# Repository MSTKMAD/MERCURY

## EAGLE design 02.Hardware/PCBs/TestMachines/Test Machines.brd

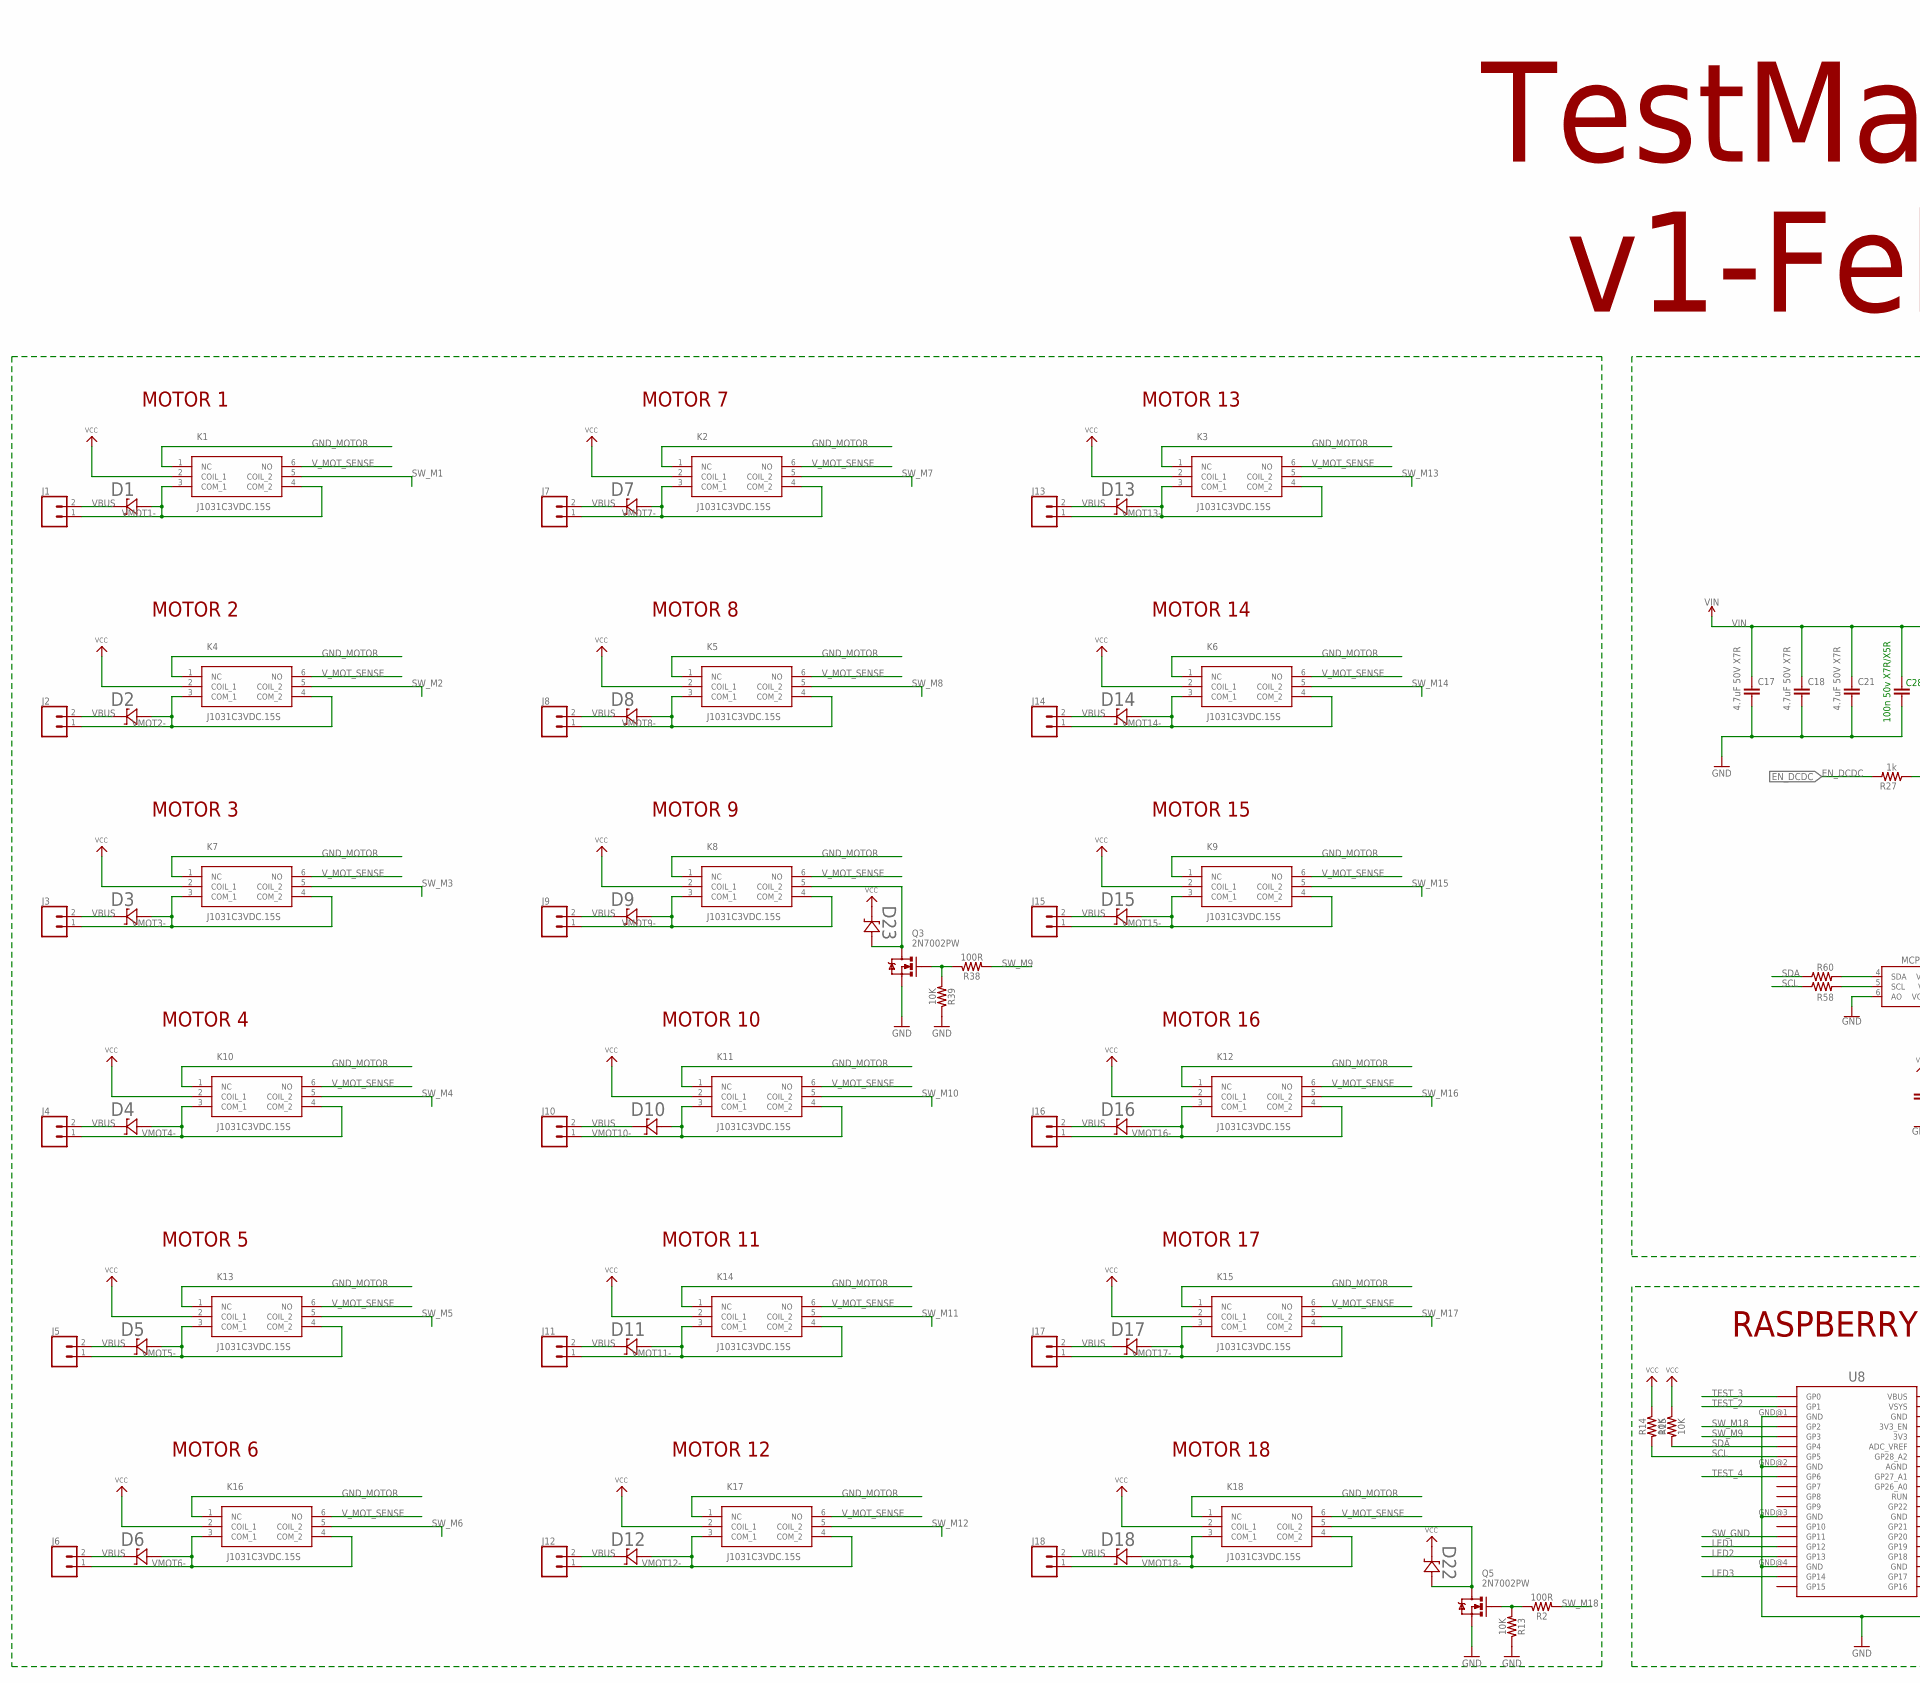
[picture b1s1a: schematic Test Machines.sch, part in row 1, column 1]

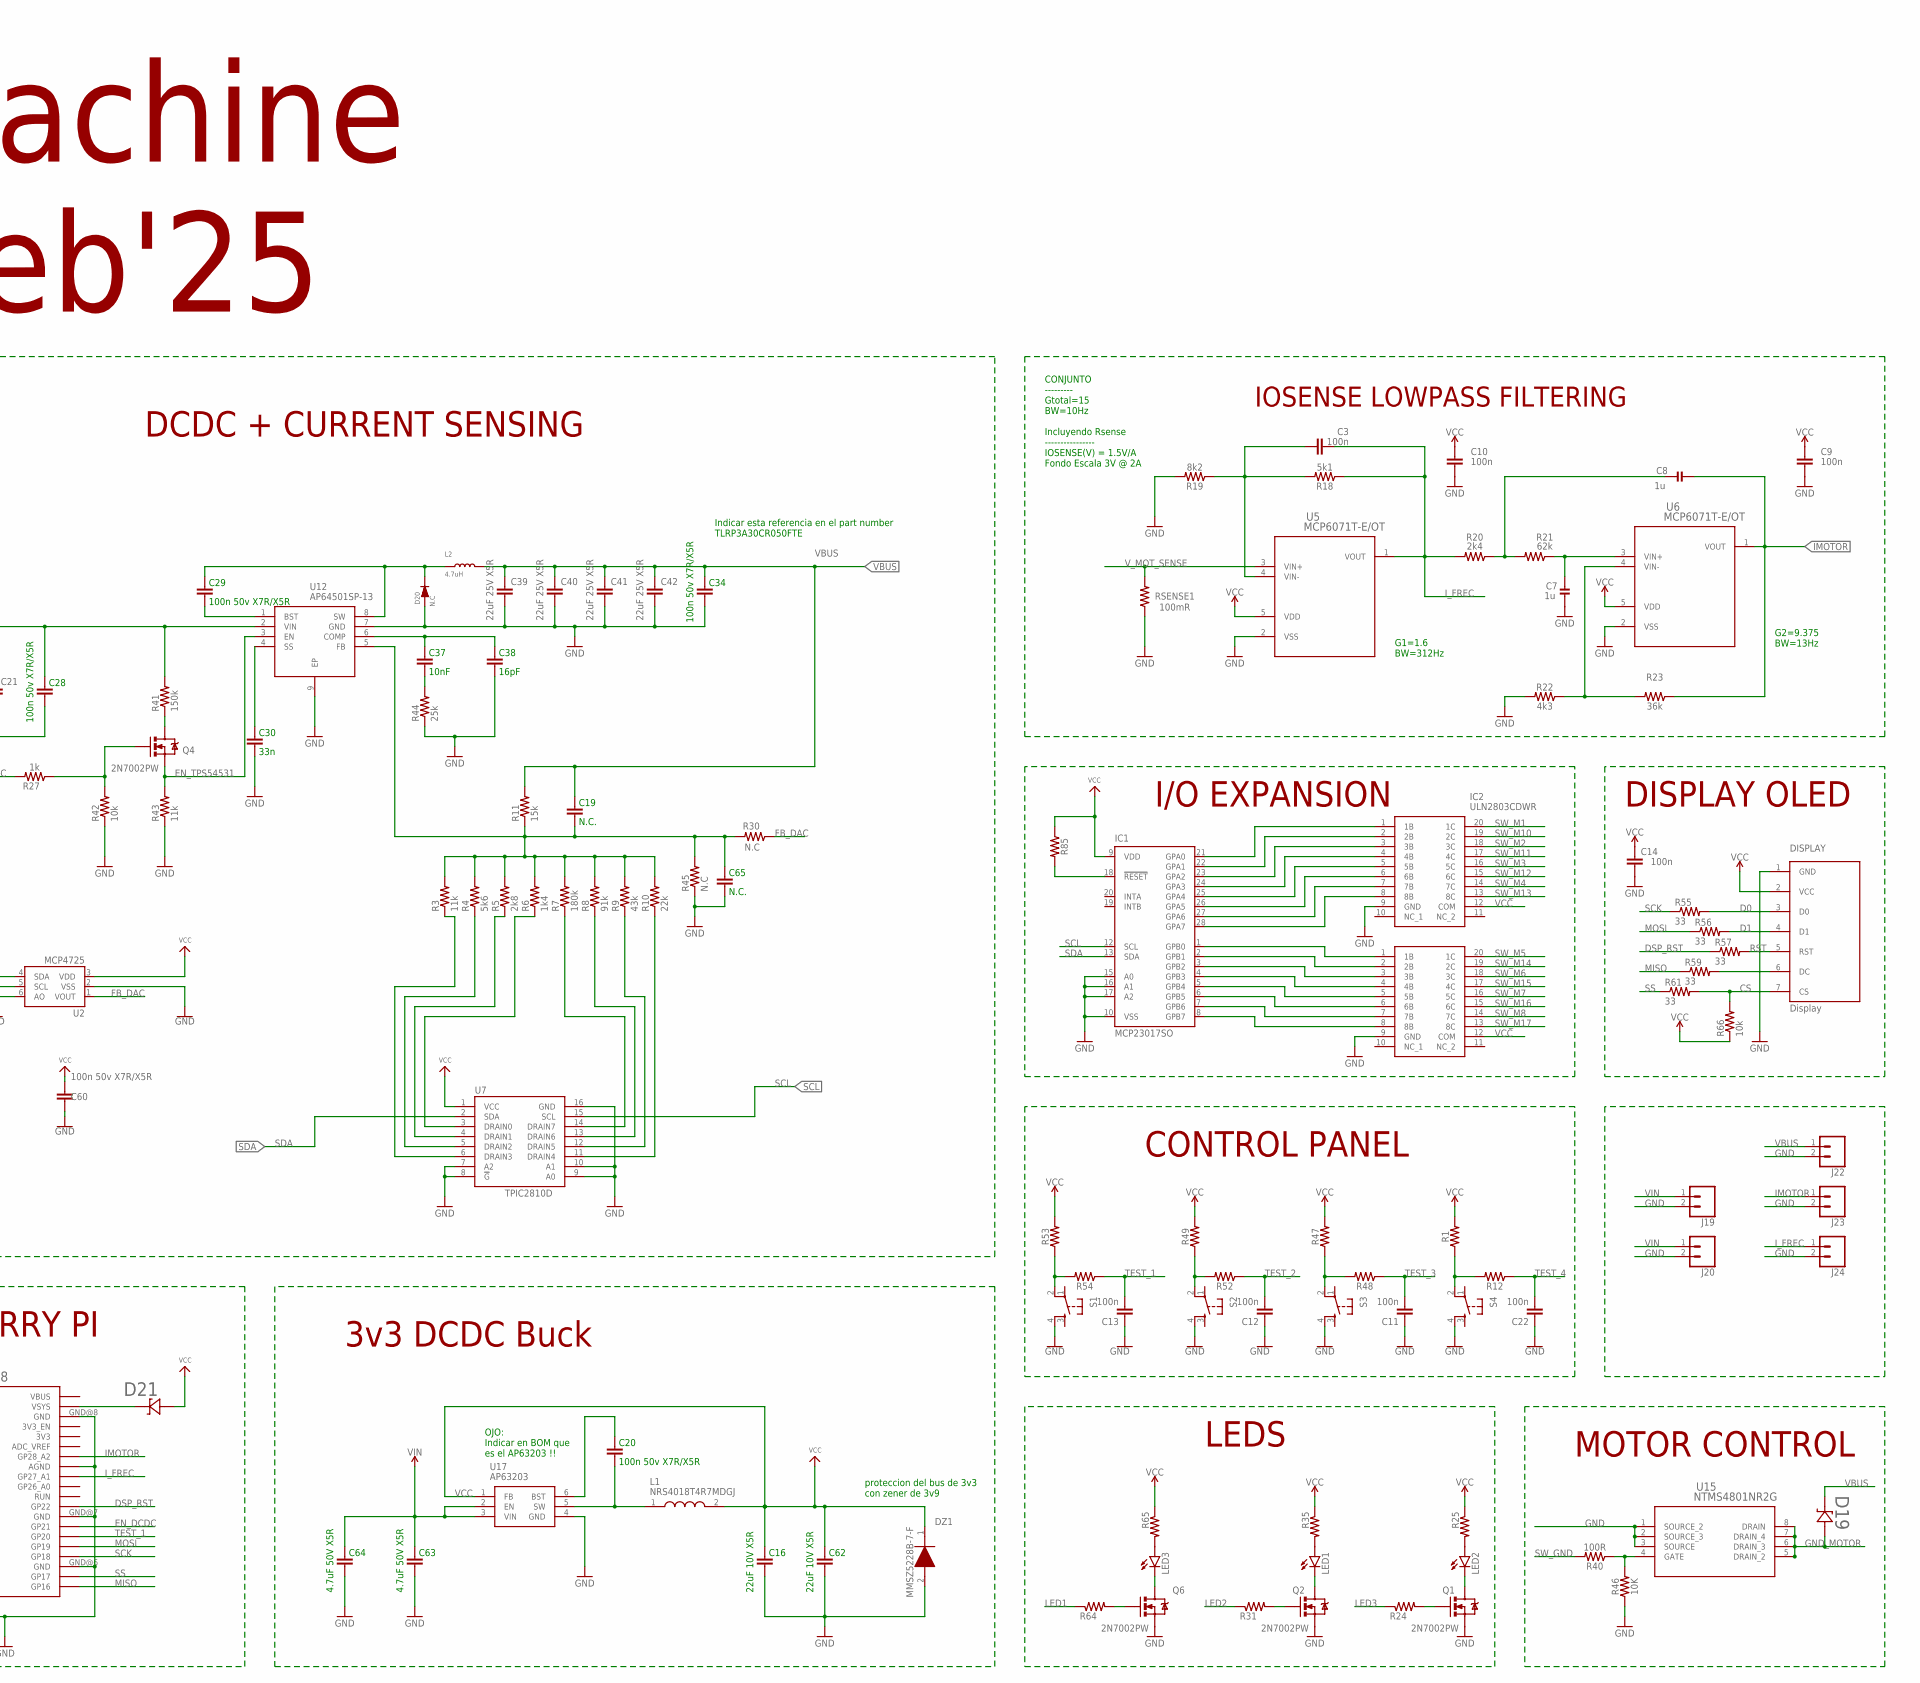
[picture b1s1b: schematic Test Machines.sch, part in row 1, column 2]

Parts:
C3, C9, C10: 100n; 0603
C7, C8: 1u; 0603-NO
C11, C12, C13, C14, C22: 100n; 0805
C16, C62: 22uF 10V X5R; 0805
C17, C18, C21: 4.7uF 50V X7R; 1210
C19, C65: N.C.; 0805
C20, C28, C29, C34, C60: 100n 50v X7R/X5R; 0805
C30: 33n; 0805
C37: 10nF; 0805
C38: 16pF; 0805
C39, C40, C41, C42: 22uF 25V X5R; 1210
C63, C64: 4.7uF 50V X5R; 0805
D1, D2, D3, D4, D5, D6, D7, D8, D9, D10, D11, D12, D13, D14, D15, D16, D17, D18, D19, D21, D22, D23: STPS1L40U; SMB_STM
D20: N.C; DO-214AB
DISPLAY: Display; OLED_LCD
DZ1: MMSZ5228B-7-F; SODFL3518X115N
IC1: MCP23017SO; SO28W
IC2, IC3: ULN2803CDWR; SOIC127P1030X265-20N
J1, J2, J3, J4, J5, J6, J7, J8, J9, J10, J11, J12, J13, J14, J15, J16, J17, J18, J19, J20, J22, J23, J24: CONN_02; 1X02
K1, K2, K3, K4, K5, K6, K7, K8, K9, K10, K11, K12, K13, K14, K15, K16, K17, K18: J1031C3VDC.15S; J1031C3VDC15S
L1: NRS4018T4R7MDGJ; NRS4018T100MDGJ
L2: 4.7uH; WE-LHMI
LED1, LED2, LED3: LED3MM
Q1, Q2, Q3, Q4, Q5, Q6: 2N7002PW; SOT323
R1, R12, R24, R25, R31, R35, R47, R48, R49, R52, R53, R54, R58, R60, R64, R65, R85: 0805
R2, R38, R40: 100R; 0805
R3, R43: 11k; 0805
R4: 5k6; 0805
R5: 2k8; 0805
R6: 1k4; 0805
R7: 180k; 0805
R8: 91k; 0805
R9: 43k; 0805
R10: 22k; 0805
R11: 15k; 0805
R13, R14, R15, R39, R46: 10K; 0805
R18: 5k1; 0805
R19: 8k2; 0805
R20: 2k4; 0805
R21: 62k; 0805
R22: 4k3; 0805
R23: 36k; 0805
R27: 1k; 0805
R30, R45: N.C; 0805
R41: 150k; 0805
R42, R66: 10k; 0805
R44: 25k; 0805
R55, R56, R57, R59, R61: 33; 0805
RSENSE1: 100mR; 1206
S1, S2, S3, S4: TAC_SWITCH_KSC931G-SMD; TAC_SW_SMD_KSC931G
U2: MCP4725; SOT23-6
U5, U6: MCP6071T-E/OT; SOT-23-5_MC_MCH
U7: TPIC2810D; SO16
U8: RPI_PICO_IG-TH; RPI_PICO_TH
U12: AP64501SP-13; SOIC127P600X163-9N
U15: NTMS4801NR2G; SOIC8_4X5_ONS
U17: AP63203; SOT95P280X100-6N

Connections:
CS: DISPLAY.7 (CS), R61.2, R66.2
D0: DISPLAY.3 (D0), R55.2
D1: DISPLAY.4 (D1), R56.2
DSP_RST: R57.1, U8.GP22
EN_DCDC: R27.2, U8.GP21
EN_TPS54531: Q4.2 (S), R43.2, U12.3 (EN)
FB_DAC: R30.1, U2.1 (VOUT)
GND: C7.2, C9.2, C10.2, C11.1, C12.1, C13.1, C14.2, C16.1, C17.2, C18.2, C21.2, C22.1, C28.1, C30.1, C34.1, C38.1, C39.2, C40.2, C41.2, C42.2, C60.1, C62.1, C63.1, C64.1, C65.1, D20.1 (A), DISPLAY.1 (GND), DZ1.2 (A), IC1.10 (VSS), IC1.15 (A0), IC1.16 (A1), IC1.17 (A2), IC2.9 (GND), IC3.9 (GND), J19.2, J20.2, J22.2, J23.2, J24.2, Q1.2 (S), Q2.2 (S), Q3.2 (S), Q5.2 (S), Q6.2 (S), R13.1, R19.2, R22.2, R39.1, R42.1, R43.1, R44.1, R45.1, R46.1, RSENSE1.1, S1.4, S2.4, S3.4, S4.4, U2.2 (VSS), U2.6 (AO), U5.2 (VSS), U6.2 (VSS), U7.7 (A2), U7.8 (!G), U7.9 (A0), U7.10 (A1), U7.16 (GND), U8.AGND, U8.GND@1 (GND), U8.GND@2 (GND), U8.GND@3 (GND), U8.GND@4 (GND), U8.GND@6 (GND), U8.GND@7 (GND), U8.GND@8 (GND), U12.7 (GND), U12.9 (EP), U15.1 (SOURCE_2), U15.2 (SOURCE_3), U15.3 (SOURCE), U17.4 (GND)
GND_MOTOR: D19.1, K1.1 (NC), K2.1 (NC), K3.1 (NC), K4.1 (NC), K5.1 (NC), K6.1 (NC), K7.1 (NC), K8.1 (NC), K9.1 (NC), K10.1 (NC), K11.1 (NC), K12.1 (NC), K13.1 (NC), K14.1 (NC), K15.1 (NC), K16.1 (NC), K17.1 (NC), K18.1 (NC), U15.5 (DRAIN_2), U15.6 (DRAIN_3), U15.7 (DRAIN_4), U15.8 (DRAIN)
IMOTOR: C8.2, J23.1, R23.1, U6.1 (VOUT), U8.GP28_A2
I_FREC: C3.1, J24.1, R18.1, R20.2, U5.1 (VOUT), U8.GP27_A1
LED1: R64.1, U8.GP12
LED2: R31.1, U8.GP13
LED3: R24.1, U8.GP14
MISO: R59.1, U8.GP16
MOSI: R56.1, U8.GP19
unnamed: R3.1, U7.6 (DRAIN3)
unnamed: R4.1, U7.5 (DRAIN2)
unnamed: R5.1, U7.4 (DRAIN1)
unnamed: R6.1, U7.3 (DRAIN0)
unnamed: R7.1, U7.14 (DRAIN7)
unnamed: R8.1, U7.13 (DRAIN6)
unnamed: R9.1, U7.12 (DRAIN5)
unnamed: R10.1, U7.11 (DRAIN4)
unnamed: R1.1, R12.2, S4.2
unnamed: LED1.A, R35.2
unnamed: LED1.K (C), Q2.3 (D)
unnamed: Q5.1 (G), R2.1, R13.2
unnamed: D22.1, K18.5 (COIL_2), Q5.3 (D)
unnamed: D23.1, K8.5 (COIL_2), Q3.3 (D)
unnamed: C3.2, R18.2, R19.1, U5.4 (VIN-)
unnamed: R22.1, R23.2, U6.4 (VIN-)
unnamed: C19.1, C65.2, R3.2, R4.2, R5.2, R6.2, R7.2, R8.2, R9.2, R10.2, R11.1, R30.2, R45.2, U12.5 (FB)
unnamed: C8.1, R20.1, R21.2
unnamed: Q2.1 (G), R31.2
unnamed: C7.1, R21.1, U6.3 (VIN+)
unnamed: Q1.1 (G), R24.2
unnamed: LED2.A, R25.2
unnamed: LED2.K (C), Q1.3 (D)
unnamed: Q3.1 (G), R38.1, R39.2
unnamed: R40.1, R46.2, U15.4 (GATE)
unnamed: Q4.3 (D), R41.1
unnamed: R47.1, R48.2, S3.2
unnamed: R49.1, R52.2, S2.2
unnamed: R53.1, R54.2, S1.2
unnamed: DISPLAY.6 (DC), R59.2
unnamed: C30.2, U12.4 (SS)
unnamed: R58.2, U2.5 (SCL)
unnamed: C29.1, U12.1 (BST)
unnamed: R60.2, U2.4 (SDA)
unnamed: C29.2, D20.2 (K), L2.1, U12.8 (SW)
unnamed: C37.2, C38.2, U12.6 (COMP)
unnamed: C37.1, R44.2
unnamed: Q6.1 (G), R64.2
unnamed: LED3.A, R65.2
unnamed: LED3.K (C), Q6.3 (D)
unnamed: C20.2, U17.6 (BST)
unnamed: C20.1, L1.1, U17.5 (SW)
unnamed: D21.2, U8.VSYS
unnamed: IC1.18 (!RESET), R85.2
unnamed: IC1.21 (GPA0), IC2.1 (1B)
unnamed: IC1.22 (GPA1), IC2.2 (2B)
unnamed: IC1.23 (GPA2), IC2.3 (3B)
unnamed: IC1.24 (GPA3), IC2.4 (4B)
unnamed: IC1.25 (GPA4), IC2.5 (5B)
unnamed: IC1.26 (GPA5), IC2.6 (6B)
unnamed: IC1.27 (GPA6), IC2.7 (7B)
unnamed: IC1.28 (GPA7), IC2.8 (8B)
unnamed: IC1.1 (GPB0), IC3.1 (1B)
unnamed: IC1.2 (GPB1), IC3.2 (2B)
unnamed: IC1.3 (GPB2), IC3.3 (3B)
unnamed: IC1.4 (GPB3), IC3.4 (4B)
unnamed: IC1.5 (GPB4), IC3.5 (5B)
unnamed: IC1.6 (GPB5), IC3.6 (6B)
unnamed: IC1.7 (GPB6), IC3.7 (7B)
unnamed: IC1.8 (GPB7), IC3.8 (8B)
RST: DISPLAY.5 (RST), R57.2
SAFETY_EN_DCDC: Q4.1 (G), R27.1, R42.2
SCK: R55.1, U8.GP18
SCL: IC1.12 (SCL), R14.2, R58.1, U7.15 (SCL), U8.GP5
SDA: IC1.13 (SDA), R15.2, R60.1, U7.2 (SDA), U8.GP4
SS: R61.1, U8.GP17
SW_GND: R40.2, U8.GP11
SW_M1: IC2.20 (1C), K1.5 (COIL_2)
SW_M2: IC2.18 (3C), K4.5 (COIL_2)
SW_M3: IC2.16 (5C), K7.5 (COIL_2)
SW_M4: IC2.14 (7C), K10.5 (COIL_2)
SW_M5: IC3.20 (1C), K13.5 (COIL_2)
SW_M6: IC3.18 (3C), K16.5 (COIL_2)
SW_M7: IC3.16 (5C), K2.5 (COIL_2)
SW_M8: IC3.14 (7C), K5.5 (COIL_2)
SW_M9: R38.2, U8.GP3
SW_M10: IC2.19 (2C), K11.5 (COIL_2)
SW_M11: IC2.17 (4C), K14.5 (COIL_2)
SW_M12: IC2.15 (6C), K17.5 (COIL_2)
SW_M13: IC2.13 (8C), K3.5 (COIL_2)
SW_M14: IC3.19 (2C), K6.5 (COIL_2)
SW_M15: IC3.17 (4C), K9.5 (COIL_2)
SW_M16: IC3.15 (6C), K12.5 (COIL_2)
SW_M17: IC3.13 (8C), K15.5 (COIL_2)
SW_M18: R2.2, U8.GP2
TEST_1: C13.2, R54.1, U8.GP20
TEST_2: C12.2, R52.1, U8.GP1
TEST_3: C11.2, R48.1, U8.GP0
TEST_4: C22.2, R12.1, U8.GP6
VBUS: C19.2, C34.2, C39.1, C40.1, C41.1, C42.1, D1.2, D2.2, D3.2, D4.2, D5.2, D6.2, D7.2, D8.2, D9.2, D10.2, D11.2, D12.2, D13.2, D14.2, D15.2, D16.2, D17.2, D18.2, D19.2, J1.2, J2.2, J3.2, J4.2, J5.2, J6.2, J7.2, J8.2, J9.2, J10.2, J11.2, J12.2, J13.2, J14.2, J15.2, J16.2, J17.2, J18.2, J22.1, L2.2, R11.2
VCC: C9.1, C10.1, C14.1, C16.2, C60.2, C62.2, D21.1, D22.2, D23.2, DISPLAY.2 (VCC), DZ1.1 (K), IC1.9 (VDD), IC2.12 (COM), IC3.12 (COM), K1.2 (COIL_1), K2.2 (COIL_1), K3.2 (COIL_1), K4.2 (COIL_1), K5.2 (COIL_1), K6.2 (COIL_1), K7.2 (COIL_1), K8.2 (COIL_1), K9.2 (COIL_1), K10.2 (COIL_1), K11.2 (COIL_1), K12.2 (COIL_1), K13.2 (COIL_1), K14.2 (COIL_1), K15.2 (COIL_1), K16.2 (COIL_1), K17.2 (COIL_1), K18.2 (COIL_1), L1.2, R1.2, R14.1, R15.1, R25.1, R35.1, R47.2, R49.2, R53.2, R65.1, R66.1, R85.1, U2.3 (VDD), U5.5 (VDD), U6.5 (VDD), U7.1 (VCC), U17.1 (FB)
VIN: C17.1, C18.1, C21.1, C28.2, C63.2, C64.2, J19.1, J20.1, R41.2, U12.2 (VIN), U17.2 (EN), U17.3 (VIN)
VMOT1-: D1.1, J1.1, K1.3 (COM_1), K1.4 (COM_2)
VMOT2-: D2.1, J2.1, K4.3 (COM_1), K4.4 (COM_2)
VMOT3-: D3.1, J3.1, K7.3 (COM_1), K7.4 (COM_2)
VMOT4-: D4.1, J4.1, K10.3 (COM_1), K10.4 (COM_2)
VMOT5-: D5.1, J5.1, K13.3 (COM_1), K13.4 (COM_2)
VMOT6-: D6.1, J6.1, K16.3 (COM_1), K16.4 (COM_2)
VMOT7-: D7.1, J7.1, K2.3 (COM_1), K2.4 (COM_2)
VMOT8-: D8.1, J8.1, K5.3 (COM_1), K5.4 (COM_2)
VMOT9-: D9.1, J9.1, K8.3 (COM_1), K8.4 (COM_2)
VMOT10-: D10.1, J10.1, K11.3 (COM_1), K11.4 (COM_2)
VMOT11-: D11.1, J11.1, K14.3 (COM_1), K14.4 (COM_2)
VMOT12-: D12.1, J12.1, K17.3 (COM_1), K17.4 (COM_2)
VMOT13-: D13.1, J13.1, K3.3 (COM_1), K3.4 (COM_2)
VMOT14-: D14.1, J14.1, K6.3 (COM_1), K6.4 (COM_2)
VMOT15-: D15.1, J15.1, K9.3 (COM_1), K9.4 (COM_2)
VMOT16-: D16.1, J16.1, K12.3 (COM_1), K12.4 (COM_2)
VMOT17-: D17.1, J17.1, K15.3 (COM_1), K15.4 (COM_2)
VMOT18-: D18.1, J18.1, K18.3 (COM_1), K18.4 (COM_2)
V_MOT_SENSE: K1.6 (NO), K2.6 (NO), K3.6 (NO), K4.6 (NO), K5.6 (NO), K6.6 (NO), K7.6 (NO), K8.6 (NO), K9.6 (NO), K10.6 (NO), K11.6 (NO), K12.6 (NO), K13.6 (NO), K14.6 (NO), K15.6 (NO), K16.6 (NO), K17.6 (NO), K18.6 (NO), RSENSE1.2, U5.3 (VIN+)

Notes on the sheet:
DCDC + CURRENT SENSING
Indicar esta referencia en el part number TLRP3A30CR050FTE
G2=9.375 BW=13Hz
G1=1.6 BW=312Hz
CONJUNTO --------- Gtotal=15 BW=10Hz Incluyendo Rsense ---------------- IOSENSE(V) = 1.5V/A Fondo Escala 3V @ 2A
IOSENSE LOWPASS FILTERING
CONTROL PANEL
DISPLAY OLED
RASPBERRY PI
LEDS
3v3 DCDC Buck
OJO: Indicar en BOM que es el AP63203 !!
proteccion del bus de 3v3 con zener de 3v9
TestMachine v1-Feb'25
MOTOR 1
MOTOR 7
MOTOR 13
MOTOR 2
MOTOR 8
MOTOR 14
MOTOR 3
MOTOR 9
MOTOR 15
MOTOR 4
MOTOR 10
MOTOR 16
MOTOR 5
MOTOR 11
MOTOR 17
MOTOR 6
MOTOR 12
MOTOR 18
I/O EXPANSION
MOTOR CONTROL

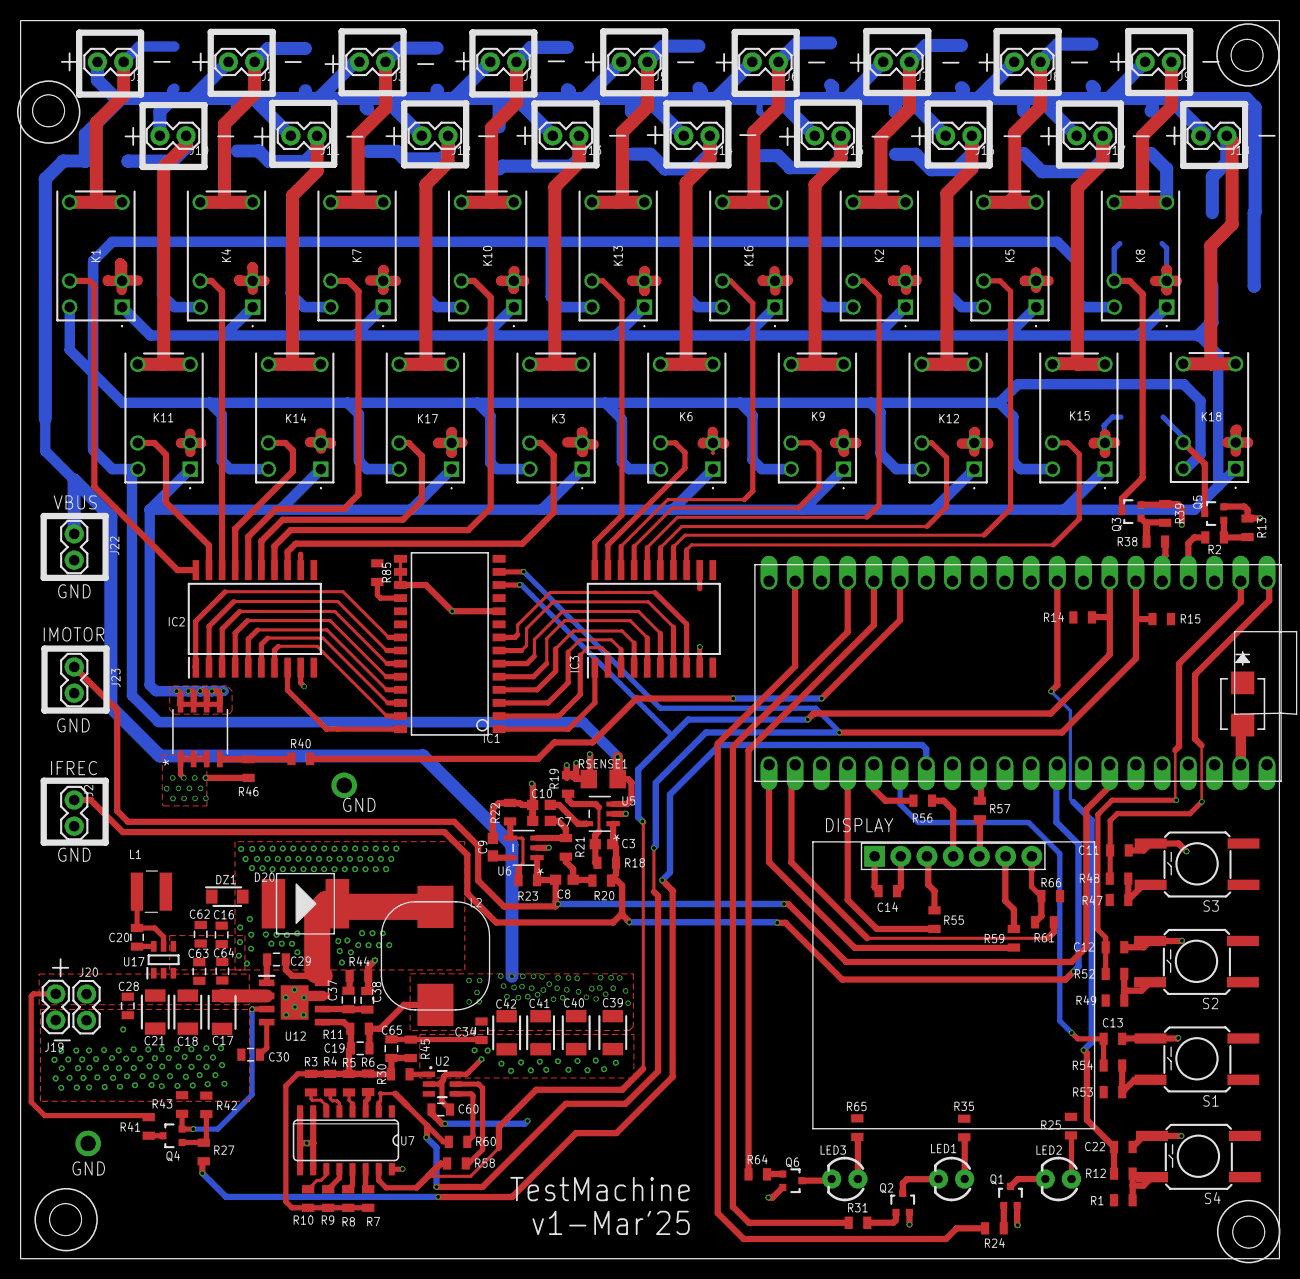
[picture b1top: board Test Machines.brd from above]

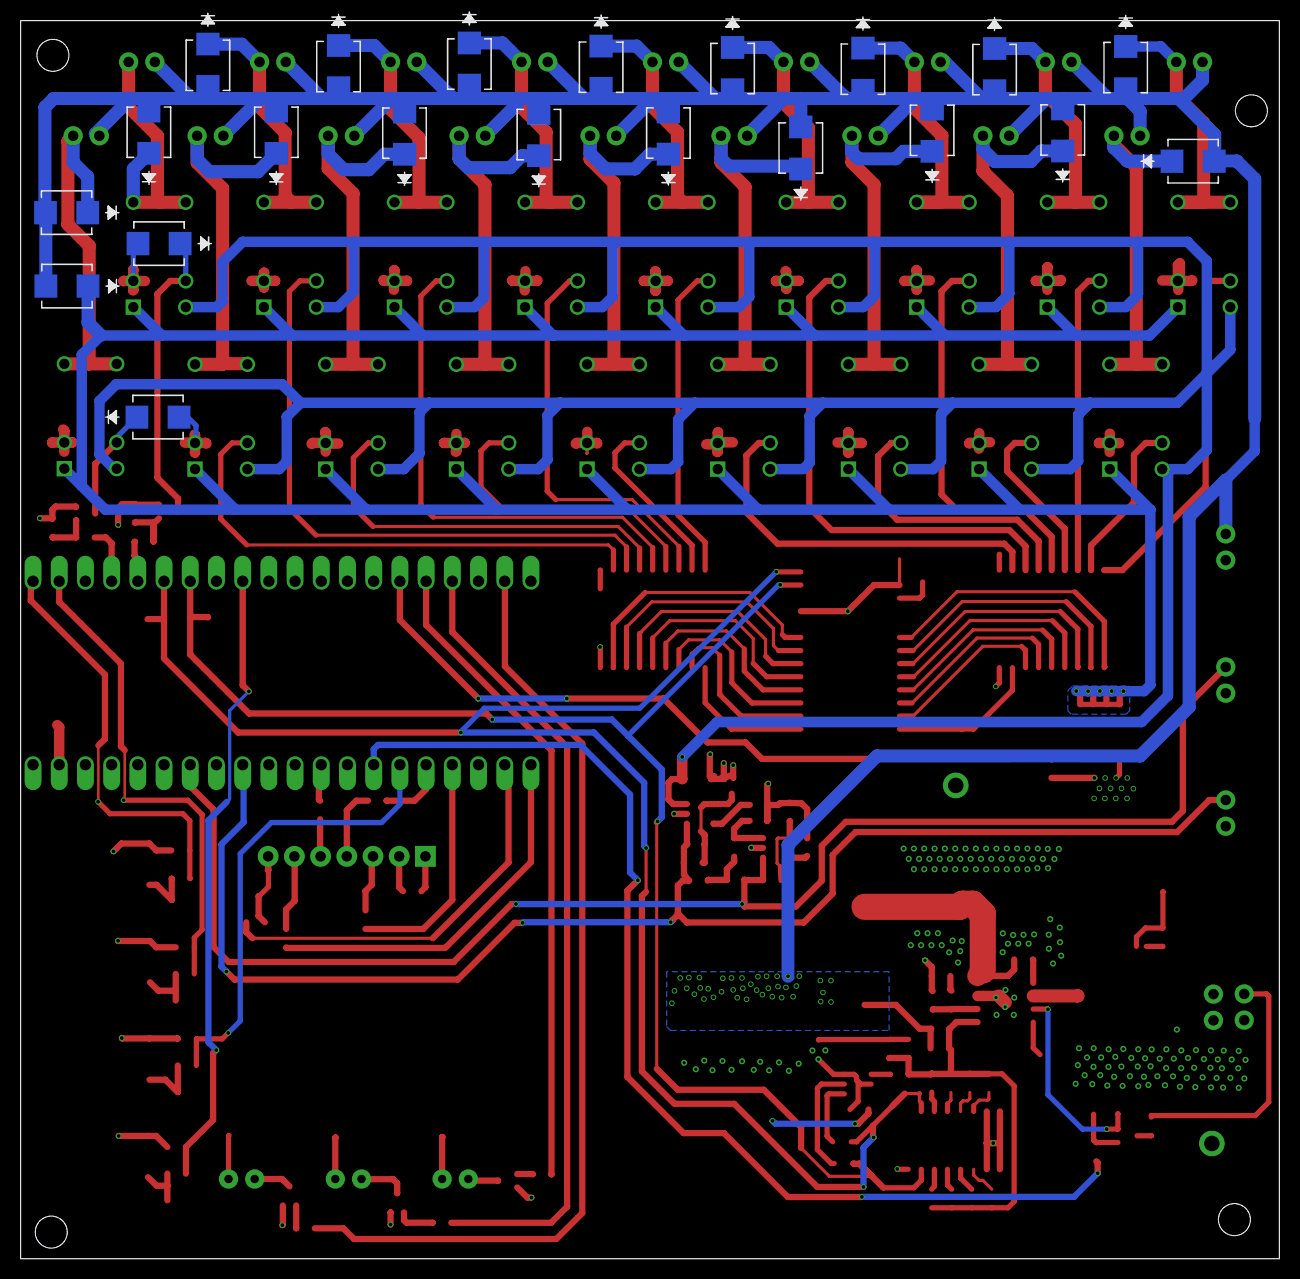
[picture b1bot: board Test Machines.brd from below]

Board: 2 copper layers, 122.0 x 120.0 mm, 177 parts (21 on the bottom side), 127 nets.

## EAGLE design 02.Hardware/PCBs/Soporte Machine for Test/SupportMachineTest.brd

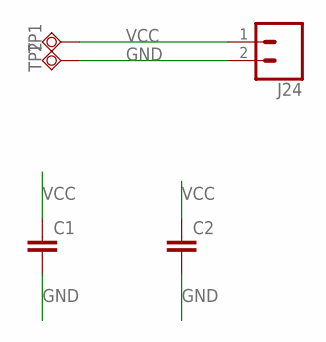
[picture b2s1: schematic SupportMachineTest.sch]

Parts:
C1: CAP-1206; 1206
C2: CAP0805; 0805
J24: CONN_02; 1X02
TP1, TP2: TESTPAD_TPSQTP20SQ; TESTPAD_TP20SQ

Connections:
GND: C1.2, C2.2, J24.2, TP2.TP
VCC: C1.1, C2.1, J24.1, TP1.TP

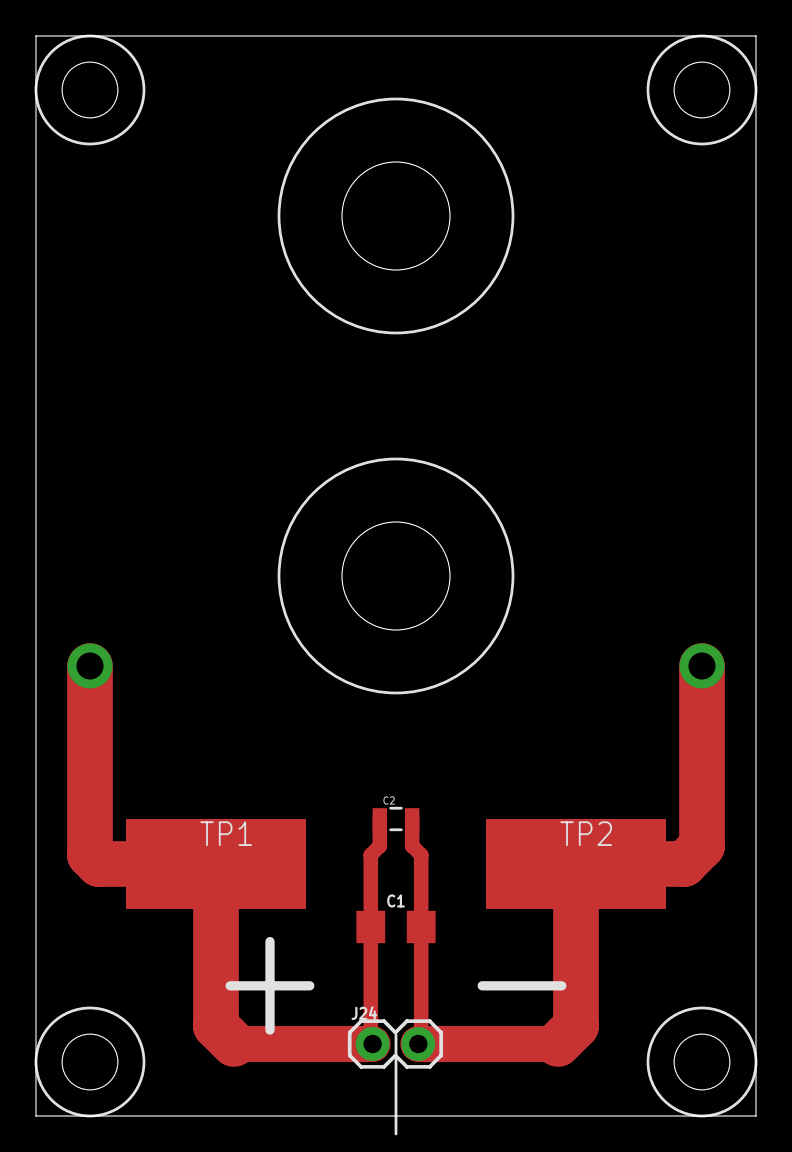
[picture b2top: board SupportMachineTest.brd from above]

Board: 2 copper layers, 40.0 x 60.0 mm, 5 parts (0 on the bottom side), 2 nets.

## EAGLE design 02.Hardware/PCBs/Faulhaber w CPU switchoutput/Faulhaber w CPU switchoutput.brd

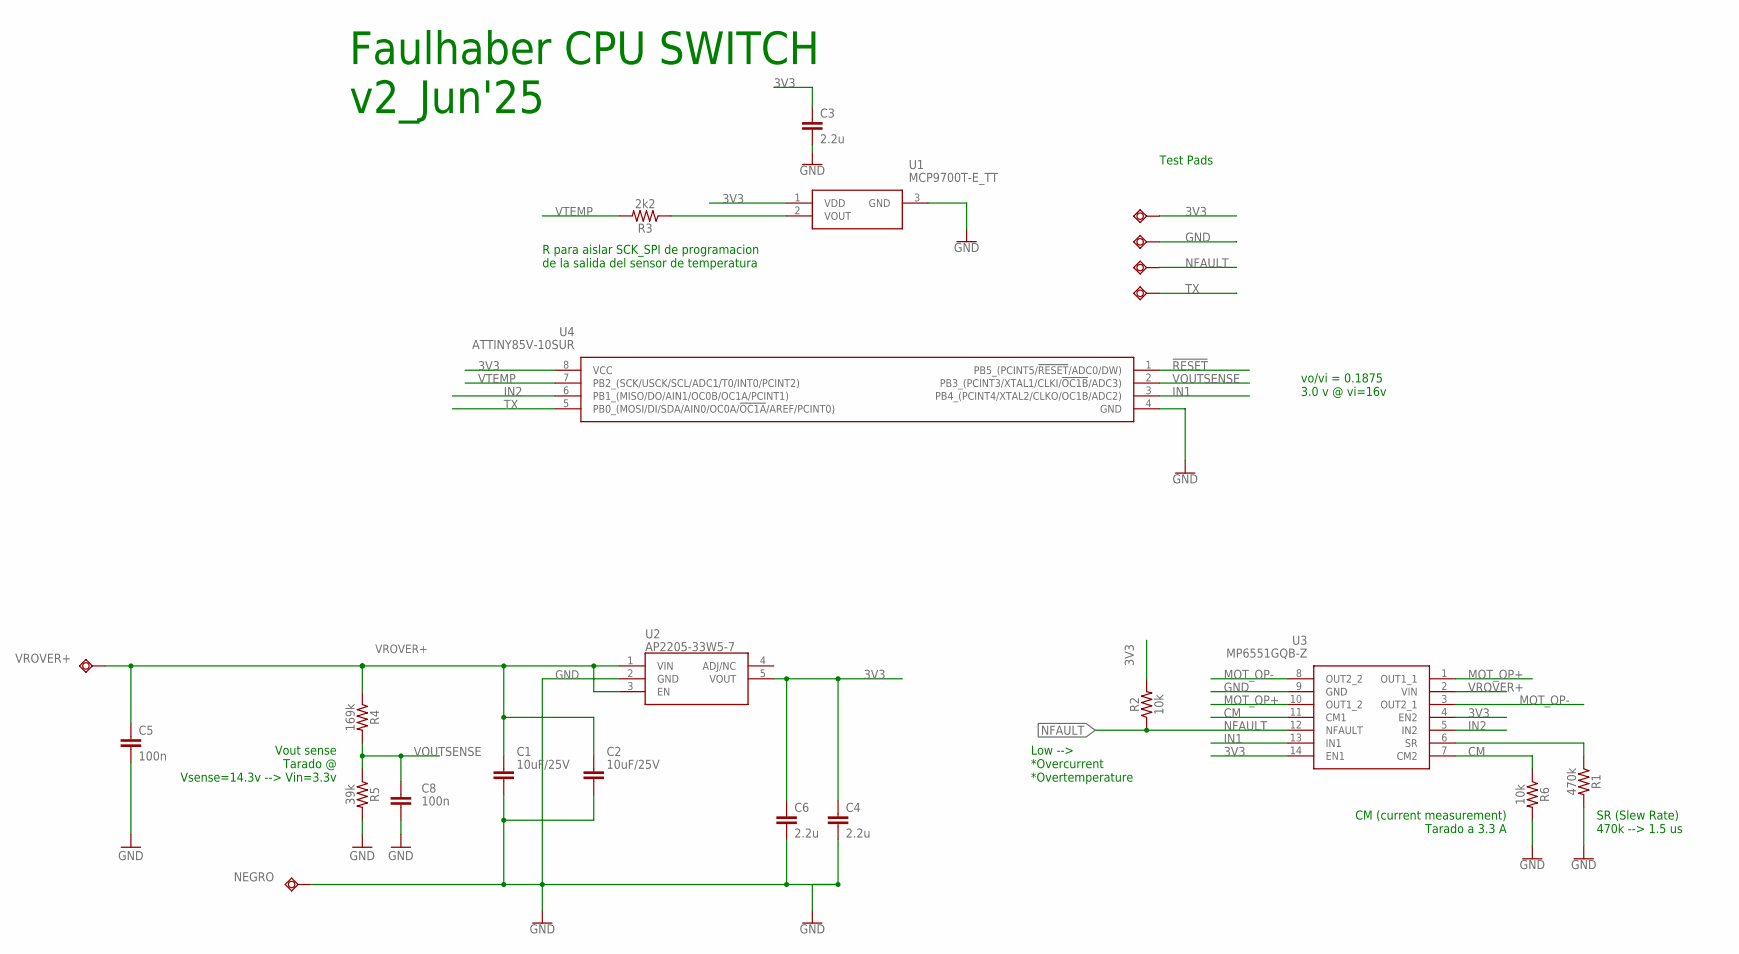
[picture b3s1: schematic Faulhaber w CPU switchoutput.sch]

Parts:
3V3: TESTPAD_TPSQB1,27; TESTPAD_B1,27
C1, C2: 10uF/25V; CAPC2012X110
C3, C4, C6: 2.2u; 0603-CAP
C5: 100n; 0603-CAP
C8: 100n; 0603
GND: TESTPAD_TPSQB1,27; TESTPAD_B1,27
NEGRO: TESTPAD_TPSQTP10SQ; TESTPAD_TP10SQ
R1: 470k; 0603
R2, R6: 10k; 0603
R3: 2k2; 0603
R4: 169k; 0603
R5: 39k; 0603
U1: MCP9700T-E_TT; SOT95P237X112-3N
U2: AP2205-33W5-7; SOT95P282X145-5N
U3: MP6551GQB-Z; MP6551GQBZ
U4: ATTINY85V-10SUR; SOIC127P798X216-8N
USB+: TESTPAD_TPSQB1,27; TESTPAD_B1,27
USB-: TESTPAD_TPSQB1,27; TESTPAD_B1,27
VROVER+: TESTPAD_TPSQTP10SQ; TESTPAD_TP10SQ

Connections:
3V3: 3V3.TP, C3.1, C4.1, C6.1, R2.2, U1.1 (VDD), U2.5 (VOUT), U3.4 (EN2), U3.14 (EN1), U4.8 (VCC)
!RESET: U4.1 (PB5_(PCINT5/!RESET!/ADC0/DW))
CM: R6.1, U3.7 (CM2), U3.11 (CM1)
GND: C1.2, C2.2, C3.2, C4.2, C5.2, C6.2, C8.2, GND.TP, NEGRO.TP, R1.2, R5.2, R6.2, U1.3 (GND), U2.2 (GND), U3.9 (GND), U4.4 (GND)
IN1: U3.13 (IN1), U4.3 (PB4_(PCINT4/XTAL2/CLKO/OC1B/ADC2))
IN2: U3.5 (IN2), U4.6 (PB1_(MISO/DO/AIN1/OC0B/OC1A/PCINT1))
MOT_OP+: U3.1 (OUT1_1), U3.10 (OUT1_2)
MOT_OP-: U3.3 (OUT2_1), U3.8 (OUT2_2)
unnamed: R3.1, U1.2 (VOUT)
unnamed: R1.1, U3.6 (SR)
NFAULT: R2.1, U3.12 (NFAULT), USB+.TP
TX: U4.5 (PB0_(MOSI/DI/SDA/AIN0/OC0A/!OC1A!/AREF/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), USB-.TP
VOUTSENSE: C8.1, R4.2, R5.1, U4.2 (PB3_(PCINT3/XTAL1/CLKI/!OC1B!/ADC3))
VROVER+: C1.1, C2.1, C5.1, R4.1, U2.1 (VIN), U2.3 (EN), U3.2 (VIN), VROVER+.TP
VTEMP: R3.2, U4.7 (PB2_(SCK/USCK/SCL/ADC1/T0/INT0/PCINT2))

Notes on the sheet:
Faulhaber CPU SWITCH v2_Jun'25
vo/vi = 0.1875 3.0 v @ vi=16v
R para aislar SCK_SPI de programacion de la salida del sensor de temperatura
Test Pads
SR (Slew Rate) 470k --> 1.5 us
CM (current measurement) Tarado a 3.3 A
Low --> *Overcurrent *Overtemperature
Vout sense Tarado @ Vsense=14.3v --> Vin=3.3v

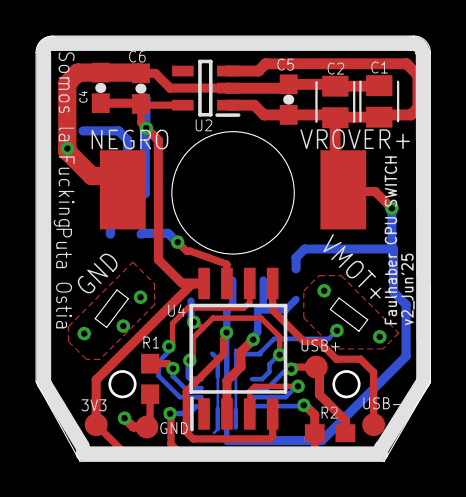
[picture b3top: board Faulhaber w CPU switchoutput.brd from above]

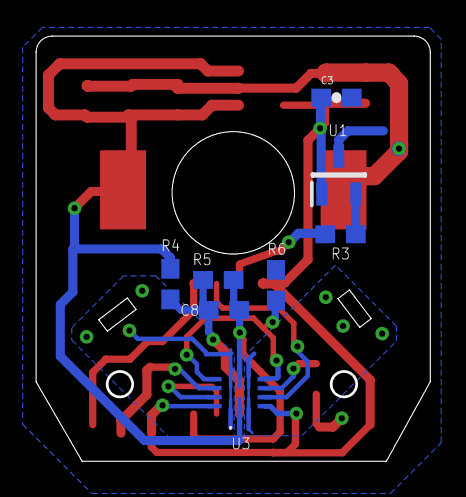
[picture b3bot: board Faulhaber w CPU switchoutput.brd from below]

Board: 2 copper layers, 21.9 x 23.6 mm, 23 parts (8 on the bottom side), 14 nets.

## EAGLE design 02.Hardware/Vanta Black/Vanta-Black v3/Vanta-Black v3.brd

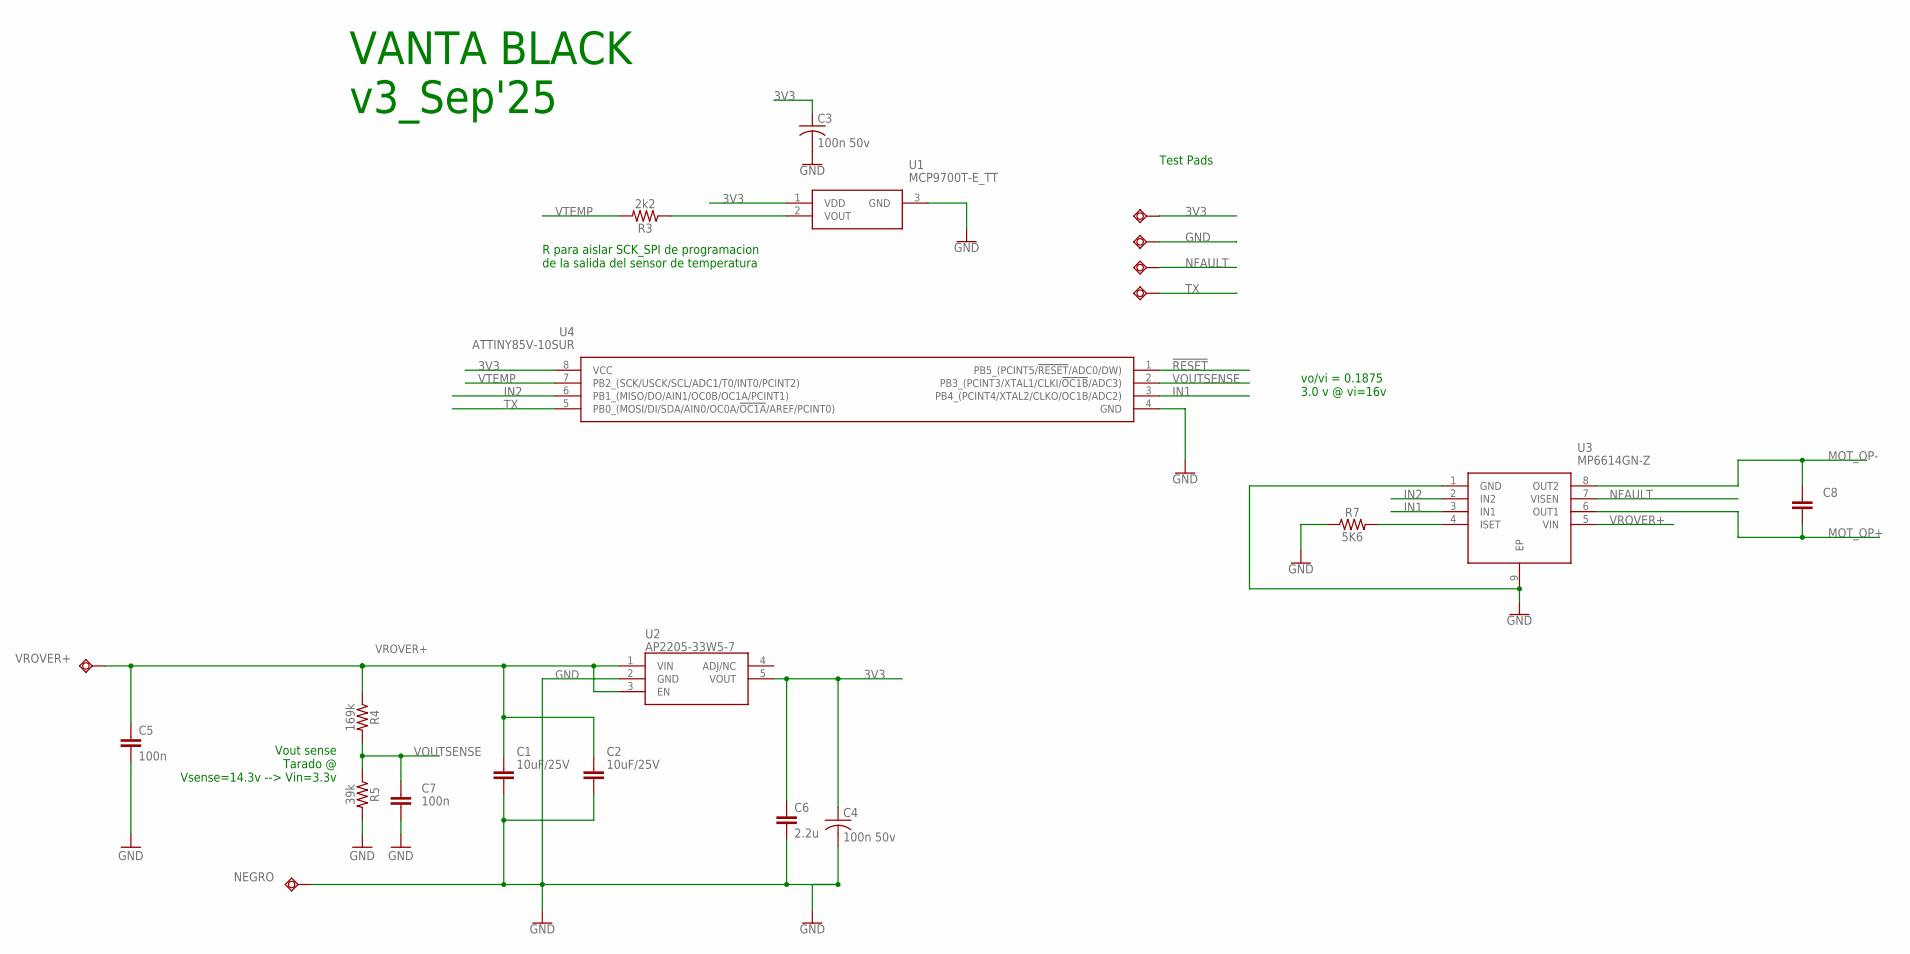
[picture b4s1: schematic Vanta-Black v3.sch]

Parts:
3V3: TESTPAD_TPSQB1,27; TESTPAD_B1,27
C1, C2: 10uF/25V; CAPC2012X110
C3, C4: 100n 50v; C0805
C5: 100n; 0603-CAP
C6: 2.2u; 0603-CAP
C7: 100n; 0603
C8: 100n; 0805
GND: TESTPAD_TPSQB1,27; TESTPAD_B1,27
NEGRO: TESTPAD_TPSQTP10SQ; TESTPAD_TP10SQ
R3: 2k2; 0603
R4: 169k; 0603
R5: 39k; 0603
R7: 5K6; 0603
TX: TESTPAD_TPSQB1,27; TESTPAD_B1,27
U1: MCP9700T-E_TT; SOT95P237X112-3N
U2: AP2205-33W5-7; SOT95P282X145-5N
U3: MP6614GN-Z; SOIC127P600X170-9N
U4: ATTINY85V-10SUR; SOIC127P798X216-8N
VISEN: TESTPAD_TPSQB1,27; TESTPAD_B1,27
VROVER+: TESTPAD_TPSQTP10SQ; TESTPAD_TP10SQ

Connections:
3V3: 3V3.TP, C3.1, C4.1, C6.1, U1.1 (VDD), U2.5 (VOUT), U4.8 (VCC)
!RESET: U4.1 (PB5_(PCINT5/!RESET!/ADC0/DW))
GND: C1.2, C2.2, C3.2, C4.2, C5.2, C6.2, C7.2, GND.TP, NEGRO.TP, R5.2, R7.1, U1.3 (GND), U2.2 (GND), U3.1 (GND), U3.9 (EP), U4.4 (GND)
IN1: U3.3 (IN1), U4.3 (PB4_(PCINT4/XTAL2/CLKO/OC1B/ADC2))
IN2: U3.2 (IN2), U4.6 (PB1_(MISO/DO/AIN1/OC0B/OC1A/PCINT1))
MOT_OP+: C8.2, U3.6 (OUT1)
MOT_OP-: C8.1, U3.8 (OUT2)
unnamed: R3.1, U1.2 (VOUT)
unnamed: R7.2, U3.4 (ISET)
NFAULT: U3.7 (VISEN), VISEN.TP
TX: TX.TP, U4.5 (PB0_(MOSI/DI/SDA/AIN0/OC0A/!OC1A!/AREF/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)
VOUTSENSE: C7.1, R4.2, R5.1, U4.2 (PB3_(PCINT3/XTAL1/CLKI/!OC1B!/ADC3))
VROVER+: C1.1, C2.1, C5.1, R4.1, U2.1 (VIN), U2.3 (EN), U3.5 (VIN), VROVER+.TP
VTEMP: R3.2, U4.7 (PB2_(SCK/USCK/SCL/ADC1/T0/INT0/PCINT2))

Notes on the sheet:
VANTA BLACK v3_Sep'25
vo/vi = 0.1875 3.0 v @ vi=16v
R para aislar SCK_SPI de programacion de la salida del sensor de temperatura
Test Pads
Vout sense Tarado @ Vsense=14.3v --> Vin=3.3v

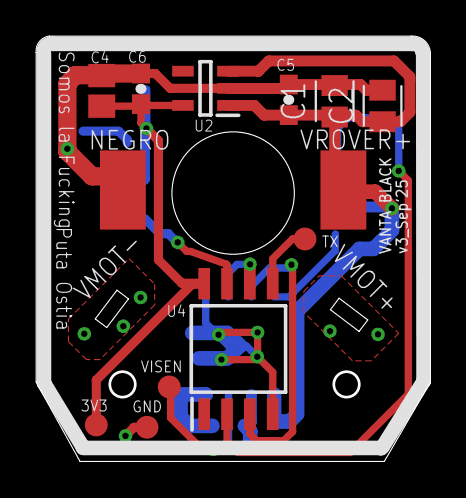
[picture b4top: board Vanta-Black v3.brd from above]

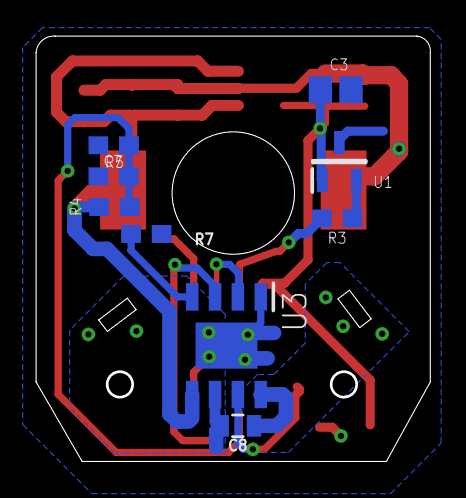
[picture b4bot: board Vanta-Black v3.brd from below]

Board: 2 copper layers, 21.9 x 23.6 mm, 22 parts (9 on the bottom side), 13 nets.

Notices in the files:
parts and their libraries:
SparkFun-Capacitors: Licensing: CC v3.0 Share-Alike You are welcome to use this library for commercial purposes.
SparkFun-Resistors: Licensing: Creative Commons ShareAlike 4.0 International - https://creativecommons.org/licenses/by-sa/4.0
